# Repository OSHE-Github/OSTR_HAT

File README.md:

# PCB design for the Open Source Thunniform Robot Project

### Check us out and find more documentation at oshe.io!

### This is the repository for the versitile Raspberry Pi HAT that was developed for the OSTR project in the Open Source Hardware Enterprise at Michigan Tech. This PCB has the following capabilities:
* Can drive two bidirectional 12 V DC motors or four unidirectional 12 V DC motors
* Can control up to two 5 V servos and read from the feedback potentiometer if it's broken out of the servo. These headers can also be used as 5 V ADC inputs
* Has three 3.3 V ADC headers with 3.3 V and GND available. Can be used to read from a potentiometer.
* Two 3.3 V PWM headers with GND and 5 V
* Two GPIO headers with GND and 3.3 V
* Two 3.3 V I2C headers, one is designed/located to be used with the MPU6050 IMU
* Screw terminal 1-wire port designed for a 1-wire based temperature sensor
* Wide input voltage range of 7 V - 30 V using a DFR1015 buck converter
* Capable of monitoring the input voltage. Useful for running off of a battery
* Capable of measuring the output current of both motor drivers (uses two DRV8874 motor drivers)
* Two audio amplifiers designed to be used with custom built piezo electric disk based transducers

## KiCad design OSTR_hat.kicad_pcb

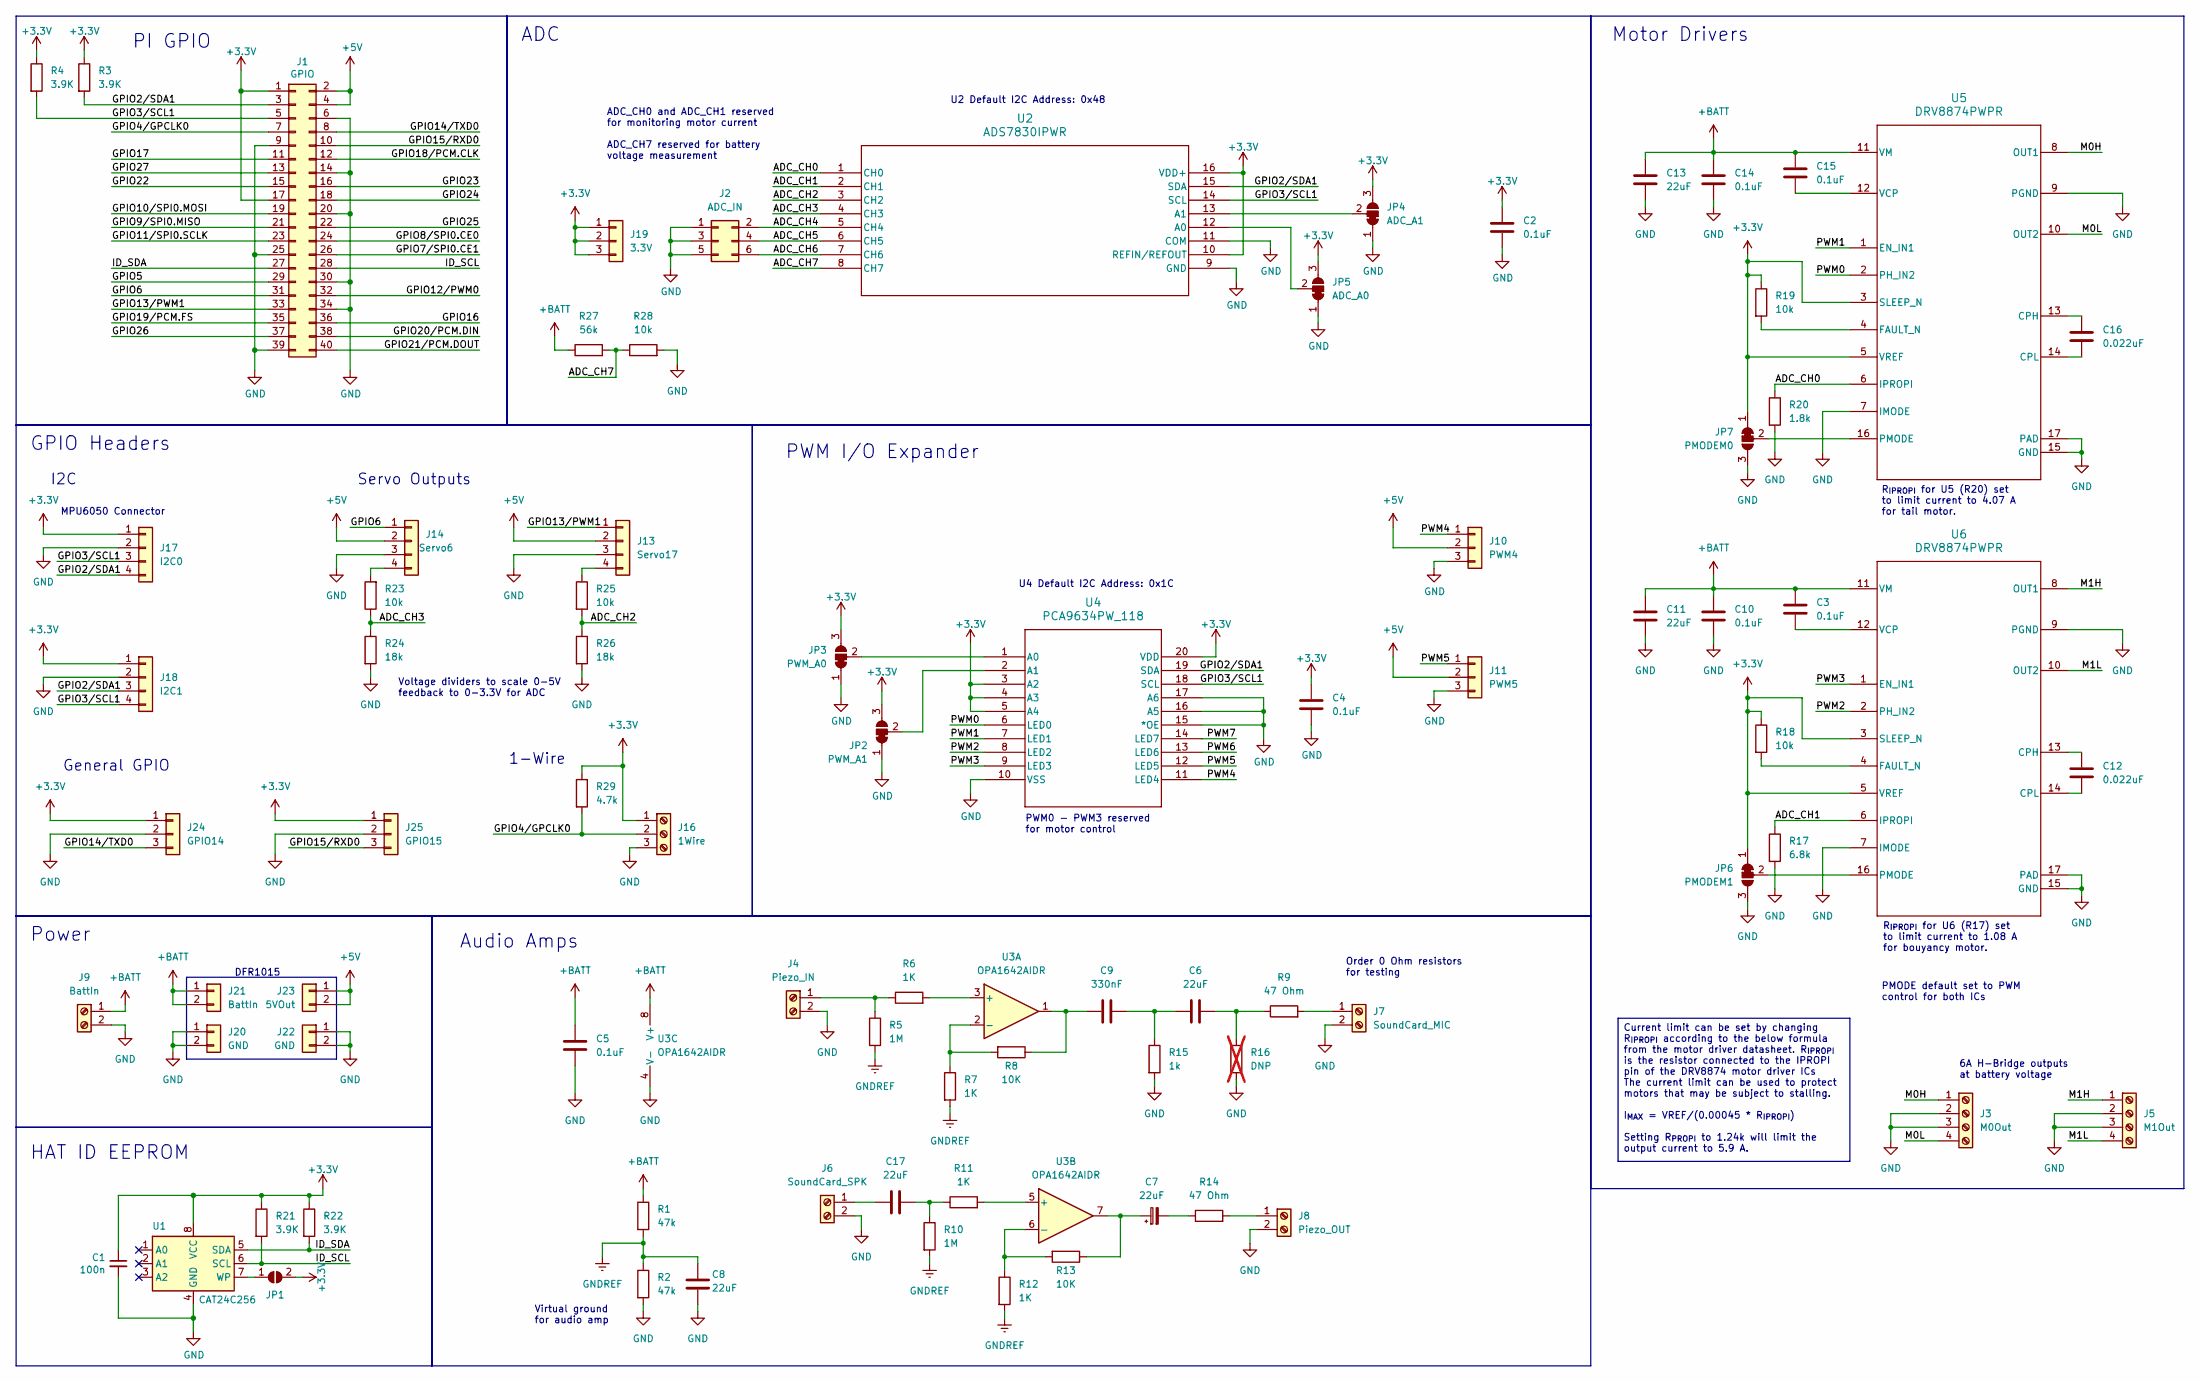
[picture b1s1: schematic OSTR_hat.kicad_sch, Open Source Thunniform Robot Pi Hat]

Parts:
C1: 100n; C_0603_1608Metric
C2, C4, C5: 0.1uF; C_0603_1608Metric
C3, C15: 0.1uF; C_0603_1608Metric; Part Number C1206C104K5RACTU
C6, C7, C8, C11, C13, C17: 22uF; C_0603_1608Metric
C9: 330nF; C_0603_1608Metric
C10, C14: 0.1uF; C_0603_1608Metric; Part Number GRM155R71C104KA88J
C12, C16: 0.022uF; C_0603_1608Metric; Part Nember C0805C223K5RACTU
J1: GPIO; PinSocket_2x20_P2.54mm_Vertical
J2: ADC_IN; PinHeader_2x03_P2.54mm_Vertical
J3: M0Out; TerminalBlock_Phoenix_MPT-0,5-4-2.54_1x04_P2.54mm_Horizontal
J4: Piezo_IN; TerminalBlock_Phoenix_MPT-0,5-2-2.54_1x02_P2.54mm_Horizontal
J5: M1Out; TerminalBlock_Phoenix_MPT-0,5-4-2.54_1x04_P2.54mm_Horizontal
J6: SoundCard_SPK; TerminalBlock_Phoenix_MPT-0,5-2-2.54_1x02_P2.54mm_Horizontal
J7: SoundCard_MIC; TerminalBlock_Phoenix_MPT-0,5-2-2.54_1x02_P2.54mm_Horizontal
J8: Piezo_OUT; TerminalBlock_Phoenix_MPT-0,5-2-2.54_1x02_P2.54mm_Horizontal
J9: BattIn; TerminalBlock_Phoenix_MKDS-1,5-2-5.08_1x02_P5.08mm_Horizont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
J10: PWM4; PinHeader_1x03_P2.54mm_Vertical
J11: PWM5; PinHeader_1x03_P2.54mm_Vertical
J13: Servo17; PinHeader_1x04_P2.54mm_Vertical
J14: Servo6; PinHeader_1x04_P2.54mm_Vertical
J16: 1Wire; TerminalBlock_Phoenix_MPT-0,5-3-2.54_1x03_P2.54mm_Horizontal
J17: I2C0; PinHeader_1x04_P2.54mm_Vertical
J18: I2C1; PinHeader_1x04_P2.54mm_Vertical
J19: 3.3V; PinHeader_1x03_P2.54mm_Vertical
J20, J22: GND; PinHeader_1x02_P2.54mm_Vertical
J21: BattIn; PinHeader_1x02_P2.54mm_Vertical
J23: 5VOut; PinHeader_1x02_P2.54mm_Vertical
J24: GPIO14; PinHeader_1x03_P2.54mm_Vertical
J25: GPIO15; PinHeader_1x03_P2.54mm_Vertical
JP1: ID_WP; SolderJumper-2_P1.3mm_Open_Pad1.0x1.5mm
JP2: PWM_A1; SolderJumper-3_P1.3mm_Bridged12_Pad1.0x1.5mm
JP3: PWM_A0; SolderJumper-3_P1.3mm_Bridged12_Pad1.0x1.5mm
JP4: ADC_A1; SolderJumper-3_P1.3mm_Bridged12_Pad1.0x1.5mm
JP5: ADC_A0; SolderJumper-3_P1.3mm_Bridged12_Pad1.0x1.5mm
JP6: PMODEM1; SolderJumper-3_P1.3mm_Bridged12_Pad1.0x1.5mm
JP7: PMODEM0; SolderJumper-3_P1.3mm_Bridged12_Pad1.0x1.5mm
R1, R2: 47k; R_0603_1608Metric
R3, R4, R21, R22: 3.9K; R_0603_1608Metric
R5, R10: 1M; R_0603_1608Metric
R6, R7, R11, R12: 1K; R_0603_1608Metric
R8, R13: 10K; R_0603_1608Metric
R9, R14: 47 Ohm; R_0603_1608Metric
R15: 1k; R_0603_1608Metric
R16: DNP; R_0603_1608Metric; not fitted
R17: 6.8k; R_0603_1608Metric
R18, R19, R23, R25, R28: 10k; R_0603_1608Metric
R20: 1.8k; R_0603_1608Metric
R24, R26: 18k; R_0603_1608Metric
R27: 56k; R_0603_1608Metric
R29: 4.7k; R_0603_1608Metric
U1: CAT24C256; SOIC127P600X175-8N
U2: ADS7830IPWR; TSSOP-16_4.4x5mm_P0.65mm
U3: OPA1642AIDR; SOIC-8_3.9x4.9mm_P1.27mm
U4: PCA9634PW_118; TSSOP-20_4.4x6.5mm_P0.65mm
U5, U6: DRV8874PWPR; PWP0016J_M

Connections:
+3.3V: C1.1, C2.1, C4.1, J1.1, J1.17, J16.1, J17.1, J18.1, J19.1, J19.2, J19.3, J24.1, J25.1, JP1.2 (B), JP2.3 (B), JP3.3 (B), JP4.3 (B), JP5.3 (B), JP6.1 (A), JP7.1 (A), R3.1, R4.1, R18.1, R19.1, R21.1, R22.1, R29.1, U1.8 (VCC), U2.10 (REFIN/REFOUT), U2.16 (VDD+), U4.3 (A2), U4.4 (A3), U4.5 (A4), U4.20 (VDD), U5.3 (SLEEP_N), U5.5 (VREF), U6.3 (SLEEP_N), U6.5 (VREF)
+5V: J1.2, J1.4, J10.2, J11.2, J13.2, J14.2, J23.1, J23.2
+BATT: C3.1, C5.1, C10.1, C11.1, C13.1, C14.1, C15.1, J9.1, J21.1, J21.2, R1.1, R27.1, U3.8 (V+), U5.11 (VM), U6.11 (VM)
/ADC_CH0: R20.1, U2.1 (CH0), U5.6 (IPROPI)
/ADC_CH1: R17.1, U2.2 (CH1), U6.6 (IPROPI)
/ADC_CH2: R25.2, R26.1, U2.3 (CH2)
/ADC_CH3: R23.1, R24.1, U2.4 (CH3)
/ADC_CH4: J2.2, U2.5 (CH4)
/ADC_CH5: J2.4, U2.6 (CH5)
/ADC_CH6: J2.6, U2.7 (CH6)
/ADC_CH7: R27.2, R28.1, U2.8 (CH7)
/GPIO2/SDA1: J1.3, J17.4, J18.3, R3.2, U2.15 (SDA), U4.19 (SDA)
/GPIO3/SCL1: J1.5, J17.3, J18.4, R4.2, U2.14 (SCL), U4.18 (SCL)
/GPIO4/GPCLK0: J1.7, J16.2, R29.2
/GPIO5: J1.29
/GPIO6: J1.31, J14.1
/GPIO7/SPI0.CE1: J1.26
/GPIO8/SPI0.CE0: J1.24
/GPIO9/SPI0.MISO: J1.21
/GPIO10/SPI0.MOSI: J1.19
/GPIO11/SPI0.SCLK: J1.23
/GPIO12/PWM0: J1.32
/GPIO13/PWM1: J1.33, J13.1
/GPIO14/TXD0: J1.8, J24.3
/GPIO15/RXD0: J1.10, J25.3
/GPIO16: J1.36
/GPIO17: J1.11
/GPIO18/PCM.CLK: J1.12
/GPIO19/PCM.FS: J1.35
/GPIO20/PCM.DIN: J1.38
/GPIO21/PCM.DOUT: J1.40
/GPIO22: J1.15
/GPIO23: J1.16
/GPIO24: J1.18
/GPIO25: J1.22
/GPIO26: J1.37
/GPIO27: J1.13
/ID_SCL: J1.28, R21.2, U1.6 (SCL)
/ID_SDA: J1.27, R22.2, U1.5 (SDA)
/M0H: J3.1, U5.8 (OUT1)
/M0L: J3.4, U5.10 (OUT2)
/M1H: J5.1, U6.8 (OUT1)
/M1L: J5.4, U6.10 (OUT2)
/PWM0: U4.6 (LED0), U5.2 (PH_IN2)
/PWM1: U4.7 (LED1), U5.1 (EN_IN1)
/PWM2: U4.8 (LED2), U6.2 (PH_IN2)
/PWM3: U4.9 (LED3), U6.1 (EN_IN1)
/PWM4: J10.1, U4.11 (LED4)
/PWM5: J11.1, U4.12 (LED5)
/PWM6: U4.13 (LED6)
/PWM7: U4.14 (LED7)
GND: C1.2, C2.2, C4.2, C5.2, C8.2, C10.2, C11.2, C13.2, C14.2, J1.6, J1.9, J1.14, J1.20, J1.25, J1.30, J1.34, J1.39, J2.1, J2.3, J2.5, J3.2, J3.3, J4.2, J5.2, J5.3, J6.2, J7.2, J8.2, J9.2, J10.3, J11.3, J13.3, J14.3, J16.3, J17.2, J18.2, J20.1, J20.2, J22.1, J22.2, J24.2, J25.2, JP2.1 (A), JP3.1 (A), JP4.1 (A), JP5.1 (A), JP6.3 (B), JP7.3 (B), R2.2, R15.2, R16.2, R17.2, R20.2, R24.2, R26.2, R28.2, U1.4 (GND), U2.9 (GND), U2.11 (COM), U3.4 (V-), U4.10 (VSS), U4.15 (*OE), U4.16 (A5), U4.17 (A6), U5.7 (IMODE), U5.9 (PGND), U5.15 (GND), U5.17 (PAD), U6.7 (IMODE), U6.9 (PGND), U6.15 (GND), U6.17 (PAD)
GNDREF: C8.1, R1.2, R2.1, R5.2, R7.2, R10.2, R12.2
unnamed: C6.1, C9.2, R15.1
unnamed: C6.2, R9.1, R16.1
unnamed: C7.1, R13.1, U3.7
unnamed: C7.2, R14.1
unnamed: C9.1, R8.1, U3.1
unnamed: C17.2, R10.1, R11.1
unnamed: J4.1, R5.1, R6.1
unnamed: C17.1, J6.1
unnamed: J7.1, R9.2
unnamed: J8.1, R14.2
unnamed: J13.4, R25.1
unnamed: J14.4, R23.2
unnamed: JP1.1 (A), U1.7 (WP)
unnamed: JP2.2 (C), U4.2 (A1)
unnamed: JP3.2 (C), U4.1 (A0)
unnamed: JP4.2 (C), U2.13 (A1)
unnamed: JP5.2 (C), U2.12 (A0)
unnamed: JP6.2 (C), U6.16 (PMODE)
unnamed: JP7.2 (C), U5.16 (PMODE)
unnamed: R6.2, U3.3 (+)
unnamed: R7.1, R8.2, U3.2 (-)
unnamed: R11.2, U3.5 (+)
unnamed: R12.1, R13.2, U3.6 (-)
unnamed: C16.1, U5.13 (CPH)
unnamed: C16.2, U5.14 (CPL)
unnamed: R19.2, U5.4 (FAULT_N)
unnamed: C15.2, U5.12 (VCP)
unnamed: C12.1, U6.13 (CPH)
unnamed: C12.2, U6.14 (CPL)
unnamed: R18.2, U6.4 (FAULT_N)
unnamed: C3.2, U6.12 (VCP)

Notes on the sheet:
U2 Default I2C Address: 0x48
PWM I/O Expander
HAT ID EEPROM
1-Wire
GPIO Headers
MPU6050 Connector
I2C
PMODE default set to PWM control for both ICs
Motor Drivers
DFR1015
PI GPIO
U4 Default I2C Address: 0x1C
Order 0 Ohm resistors for testing
Voltage dividers to scale 0-5V feedback to 0-3.3V for ADC
R_{IPROPI} for U6 (R17) set to limit current to 1.08 A for bouyancy motor.
Power
6A H-Bridge outputs at battery voltage
ADC
General GPIO
R_{IPROPI} for U5 (R20) set to limit current to 4.07 A for tail motor.
Virtual ground for audio amp
Audio Amps
ADC_CH0 and ADC_CH1 reserved for monitoring motor current ADC_CH7 reserved for battery voltage measurement
PWM0 - PWM3 reserved for motor control
Servo Outputs
Current limit can be set by changing R_{IPROPI} according to the below formula from the motor driver datasheet. R_{IPROPI} is the resistor connected to the IPROPI pin of the DRV8874 motor driver ICs The current limit can be used to protect motors that may be subject to stalling. I_{MAX} = VREF/(0.0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

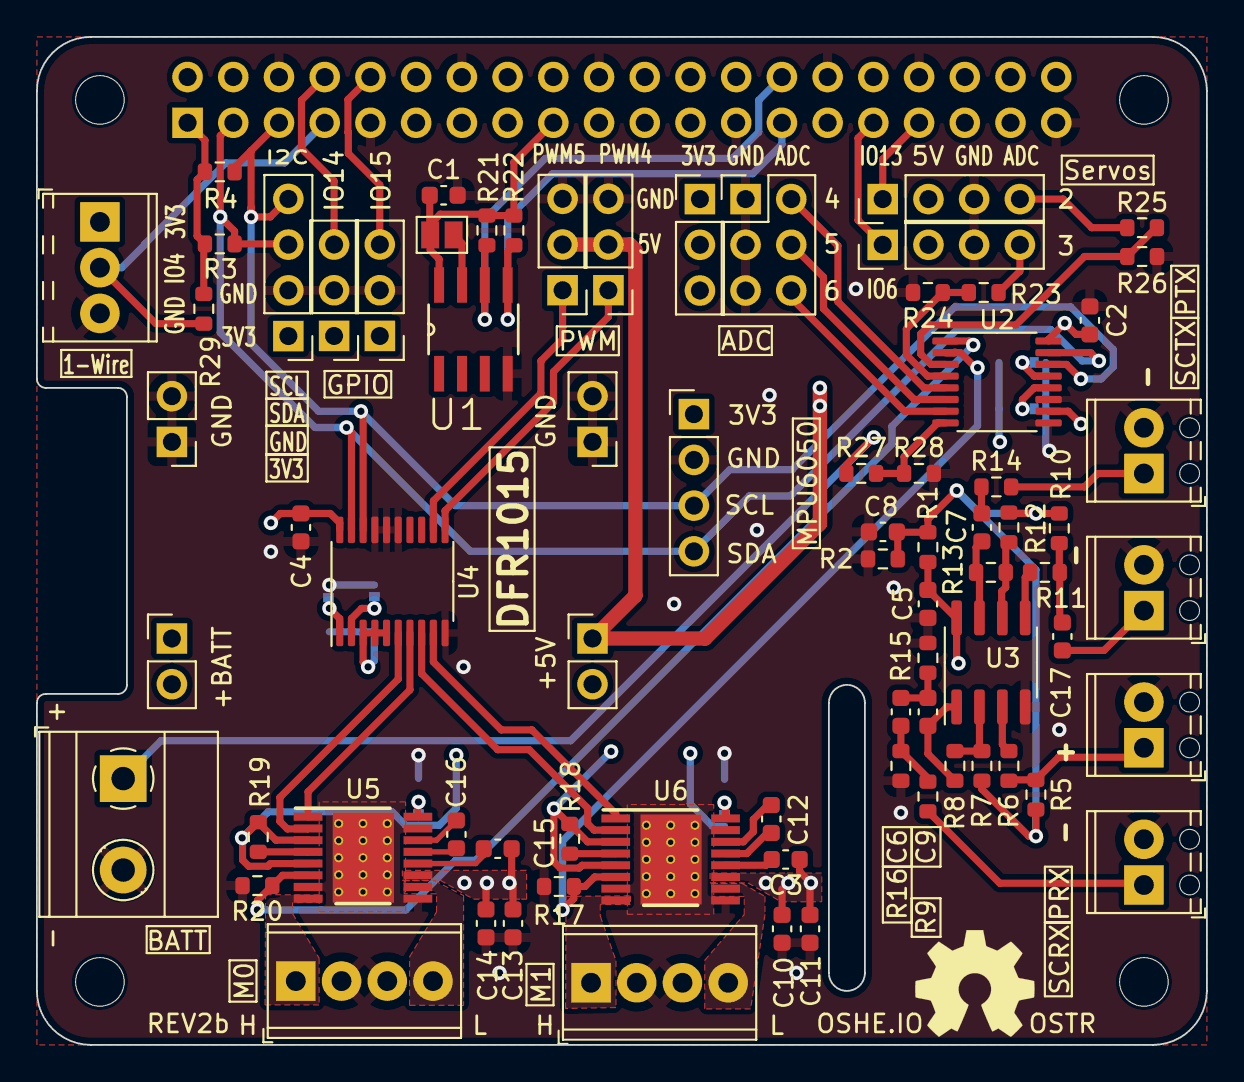
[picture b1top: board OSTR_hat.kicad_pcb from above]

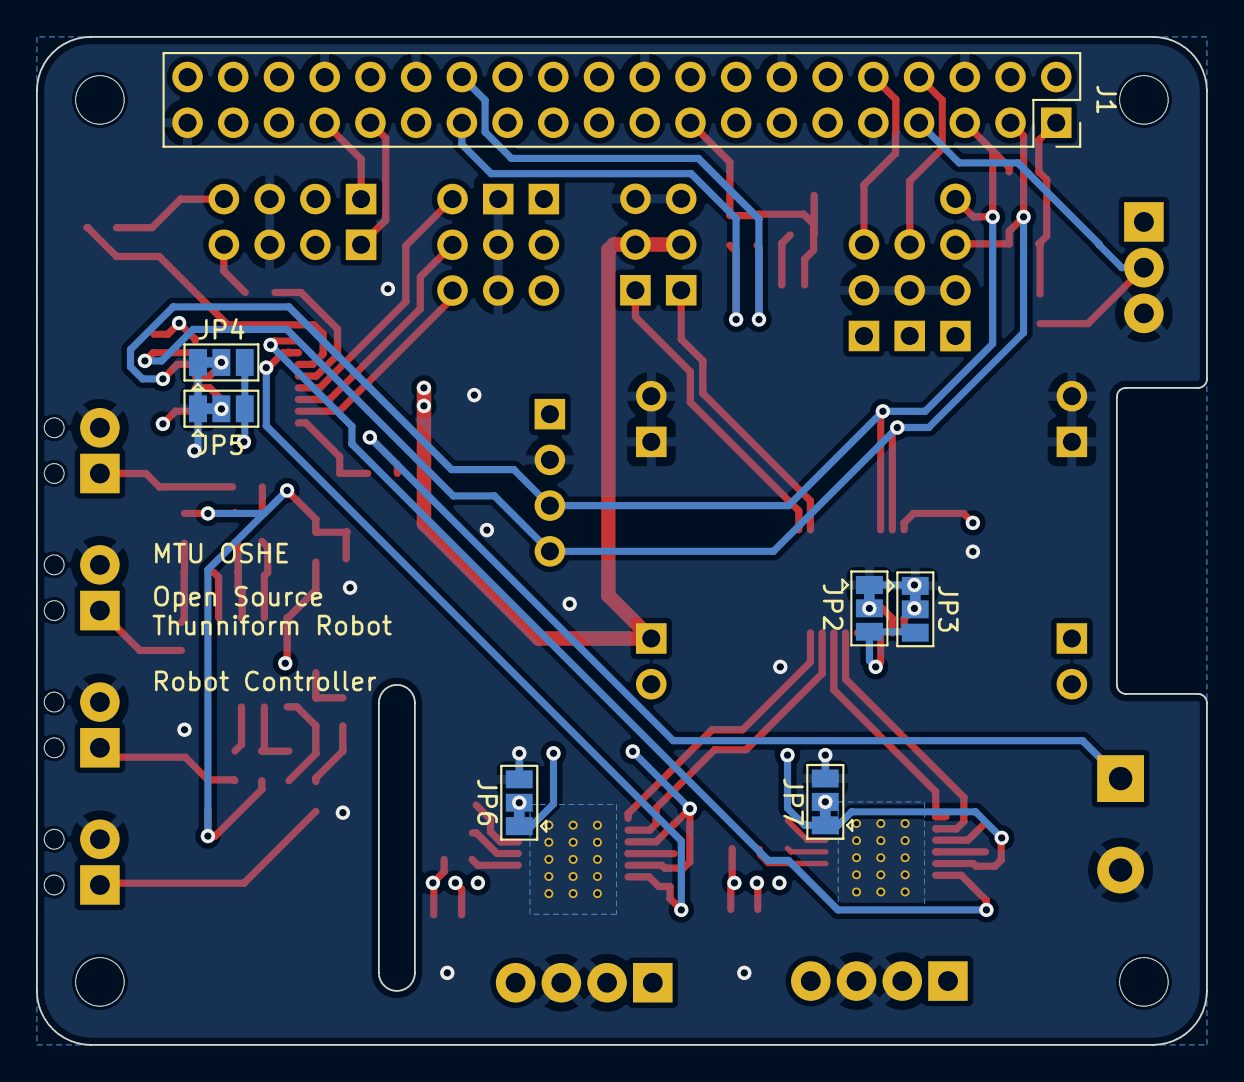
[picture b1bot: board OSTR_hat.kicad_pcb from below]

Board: 4 copper layers, 65.0 x 56.0 mm, 86 parts (7 on the bottom side), 63 nets.

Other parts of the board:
MH1, MH2, MH3, MH4: MountingHole_2.7mm_M2.5

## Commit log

2025-04-16 removed imports for IMU, servos, and temp sensor. Added comments for recommended libraries for them
2025-04-17 Generated new gerbers
2025-04-26 Added README
2025-04-26 Added stackup and description to PCB design
2025-04-26 Updated rev2b gerbers
